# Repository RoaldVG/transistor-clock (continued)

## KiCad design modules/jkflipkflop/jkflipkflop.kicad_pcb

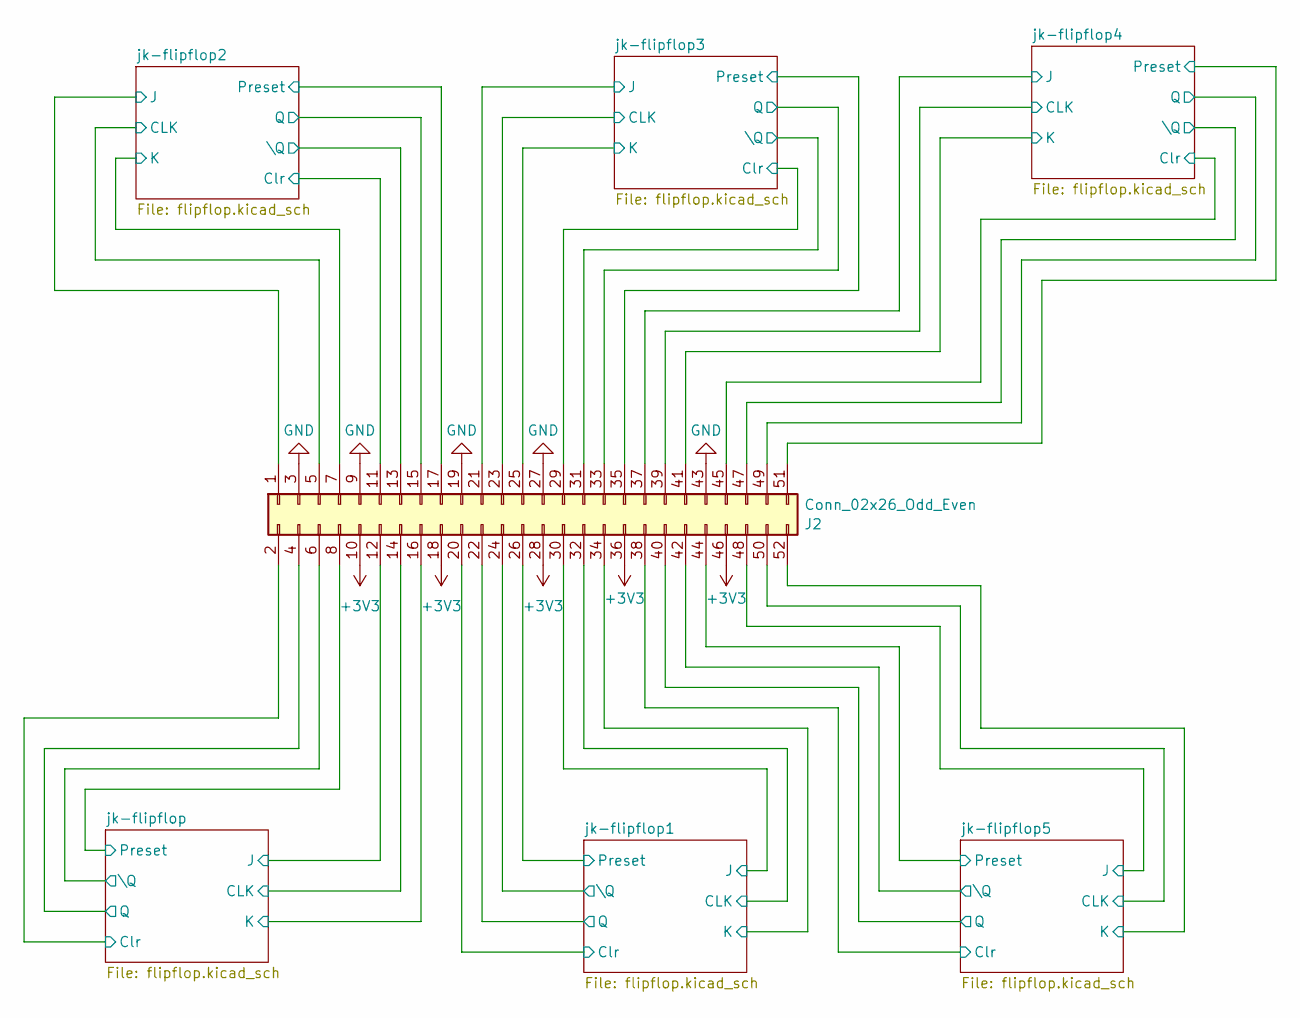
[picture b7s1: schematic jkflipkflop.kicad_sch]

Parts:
J2: Conn_02x26_Odd_Even; mpcie-full-card

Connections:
+3V3: J2.10, J2.18, J2.28, J2.36, J2.46; also elsewhere on the board
/jk-flipflop1/CLK: J2.32; also elsewhere on the board
/jk-flipflop1/Clr: J2.20; also elsewhere on the board
/jk-flipflop1/J: J2.30; also elsewhere on the board
/jk-flipflop1/K: J2.34; also elsewhere on the board
/jk-flipflop1/Preset: J2.26; also elsewhere on the board
/jk-flipflop1/Q: J2.22; also elsewhere on the board
/jk-flipflop1/\Q: J2.24; also elsewhere on the board
/jk-flipflop2/CLK: J2.5; also elsewhere on the board
/jk-flipflop2/Clr: J2.11; also elsewhere on the board
/jk-flipflop2/J: J2.1; also elsewhere on the board
/jk-flipflop2/K: J2.7; also elsewhere on the board
/jk-flipflop2/Preset: J2.17; also elsewhere on the board
/jk-flipflop2/Q: J2.15; also elsewhere on the board
/jk-flipflop2/\Q: J2.13; also elsewhere on the board
/jk-flipflop3/CLK: J2.23; also elsewhere on the board
/jk-flipflop3/Clr: J2.29; also elsewhere on the board
/jk-flipflop3/J: J2.21; also elsewhere on the board
/jk-flipflop3/K: J2.25; also elsewhere on the board
/jk-flipflop3/Preset: J2.35; also elsewhere on the board
/jk-flipflop3/Q: J2.33; also elsewhere on the board
/jk-flipflop3/\Q: J2.31; also elsewhere on the board
/jk-flipflop4/CLK: J2.39; also elsewhere on the board
/jk-flipflop4/Clr: J2.45; also elsewhere on the board
/jk-flipflop4/J: J2.37; also elsewhere on the board
/jk-flipflop4/K: J2.41; also elsewhere on the board
/jk-flipflop4/Preset: J2.51; also elsewhere on the board
/jk-flipflop4/Q: J2.49; also elsewhere on the board
/jk-flipflop4/\Q: J2.47; also elsewhere on the board
/jk-flipflop5/CLK: J2.50; also elsewhere on the board
/jk-flipflop5/Clr: J2.38; also elsewhere on the board
/jk-flipflop5/J: J2.48; also elsewhere on the board
/jk-flipflop5/K: J2.52; also elsewhere on the board
/jk-flipflop5/Preset: J2.44; also elsewhere on the board
/jk-flipflop5/Q: J2.40; also elsewhere on the board
/jk-flipflop5/\Q: J2.42; also elsewhere on the board
/jk-flipflop/CLK: J2.14; also elsewhere on the board
/jk-flipflop/Clr: J2.2; also elsewhere on the board
/jk-flipflop/J: J2.12; also elsewhere on the board
/jk-flipflop/K: J2.16; also elsewhere on the board
/jk-flipflop/Preset: J2.8; also elsewhere on the board
/jk-flipflop/Q: J2.4; also elsewhere on the board
/jk-flipflop/\Q: J2.6; also elsewhere on the board
GND: J2.3, J2.9, J2.19, J2.27, J2.43; also elsewhere on the board

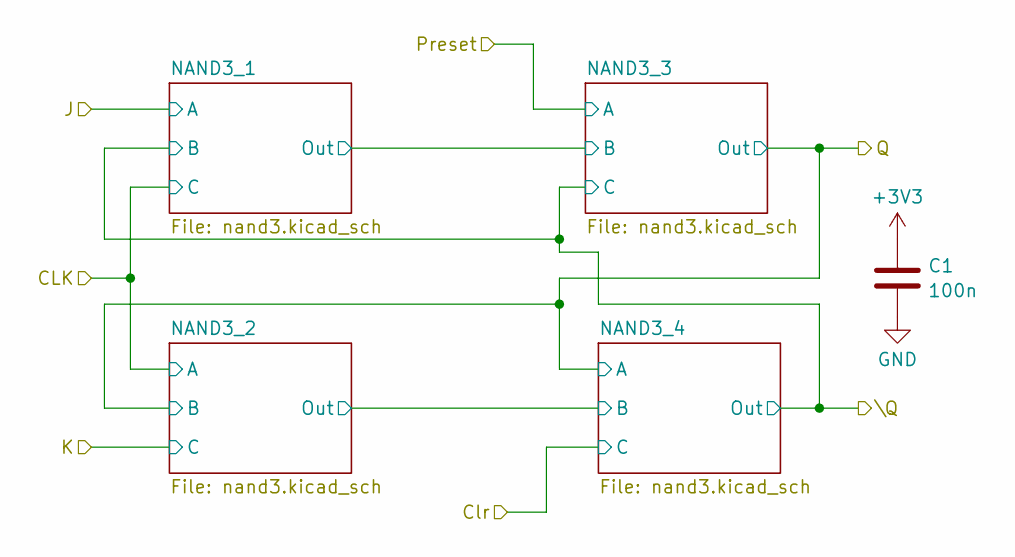
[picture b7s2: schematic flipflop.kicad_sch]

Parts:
C1: 100n; C_0603_1608Metric

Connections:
+3V3: C1.1; also elsewhere on the board
GND: C1.2; also elsewhere on the board

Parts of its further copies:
C2, C3, C4, C5, C6: 100n; C_0603_1608Metric

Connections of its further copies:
+3V3: C2.1, C3.1, C4.1, C5.1, C6.1; also elsewhere on the board
GND: C2.2, C3.2, C4.2, C5.2, C6.2; also elsewhere on the board

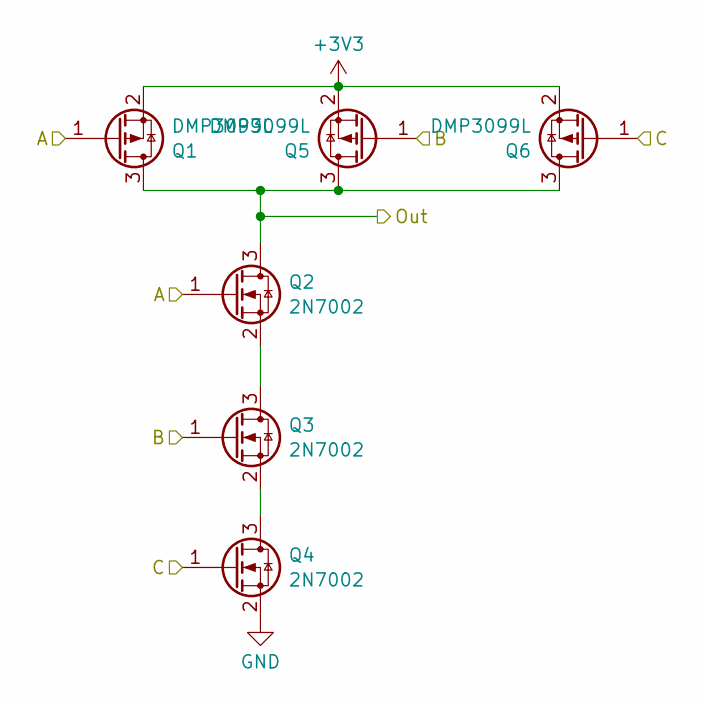
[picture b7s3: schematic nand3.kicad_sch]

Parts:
Q1, Q5, Q6: DMP3099L; SOT-23
Q2, Q3, Q4: 2N7002; SOT-23

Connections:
+3V3: Q1.2 (S), Q5.2 (S), Q6.2 (S); also elsewhere on the board
/jk-flipflop1/CLK: Q1.1 (G), Q2.1 (G); also elsewhere on the board
/jk-flipflop1/K: Q4.1 (G), Q6.1 (G); also elsewhere on the board
/jk-flipflop1/NAND3_2/Out: Q1.3 (D), Q2.3 (D), Q5.3 (D), Q6.3 (D); also elsewhere on the board
/jk-flipflop1/Q: Q3.1 (G), Q5.1 (G); also elsewhere on the board
GND: Q4.2 (S); also elsewhere on the board
unnamed: Q2.2 (S), Q3.3 (D)
unnamed: Q3.2 (S), Q4.3 (D)

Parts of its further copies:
Q7, Q11, Q12, Q13, Q17, Q18, Q19, Q23, Q24, Q25, Q29, Q30, Q31, Q35, Q36, Q37, Q41, Q42, Q43, Q47, Q48, Q49, Q50, Q57, Q58, Q59, Q60, Q61, Q62, Q69, Q70, Q71, Q72, Q73, Q74, Q81, Q82, Q83, Q84, Q85, Q86, Q93, Q94, Q95, Q96, Q97, Q101, Q102, Q103, Q107, Q108, Q109, Q113, Q114, Q115, Q119, Q120, Q121, Q125, Q126, Q127, Q131, Q132, Q133, Q137, Q138, Q139, Q143, Q144: DMP3099L; SOT-23
Q8, Q9, Q10, Q14, Q15, Q16, Q20, Q21, Q22, Q26, Q27, Q28, Q32, Q33, Q34, Q38, Q39, Q40, Q44, Q45, Q46, Q51, Q52, Q53, Q54, Q55, Q56, Q63, Q64, Q65, Q66, Q67, Q68, Q75, Q76, Q77, Q78, Q79, Q80, Q87, Q88, Q89, Q90, Q91, Q92, Q98, Q99, Q100, Q104, Q105, Q106, Q110, Q111, Q112, Q116, Q117, Q118, Q122, Q123, Q124, Q128, Q129, Q130, Q134, Q135, Q136, Q140, Q141, Q142: 2N7002; SOT-23

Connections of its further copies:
+3V3: Q7.2 (S), Q11.2 (S), Q12.2 (S), Q13.2 (S), Q17.2 (S), Q18.2 (S), Q19.2 (S), Q23.2 (S), Q24.2 (S), Q25.2 (S), Q29.2 (S), Q30.2 (S), Q31.2 (S), Q35.2 (S), Q36.2 (S), Q37.2 (S), Q41.2 (S), Q42.2 (S), Q43.2 (S), Q47.2 (S), Q48.2 (S), Q49.2 (S), Q50.2 (S), Q57.2 (S), Q58.2 (S), Q59.2 (S), Q60.2 (S), Q61.2 (S), Q62.2 (S), Q69.2 (S), Q70.2 (S), Q71.2 (S), Q72.2 (S), Q73.2 (S), Q74.2 (S), Q81.2 (S), Q82.2 (S), Q83.2 (S), Q84.2 (S), Q85.2 (S), Q86.2 (S), Q93.2 (S), Q94.2 (S), Q95.2 (S), Q96.2 (S), Q97.2 (S), Q101.2 (S), Q102.2 (S), Q103.2 (S), Q107.2 (S), Q108.2 (S), Q109.2 (S), Q113.2 (S), Q114.2 (S), Q115.2 (S), Q119.2 (S), Q120.2 (S), Q121.2 (S), Q125.2 (S), Q126.2 (S), Q127.2 (S), Q131.2 (S), Q132.2 (S), Q133.2 (S), Q137.2 (S), Q138.2 (S), Q139.2 (S), Q143.2 (S), Q144.2 (S); also elsewhere on the board
/jk-flipflop1/CLK: Q10.1 (G), Q12.1 (G); also elsewhere on the board
/jk-flipflop1/Clr: Q46.1 (G), Q48.1 (G); also elsewhere on the board
/jk-flipflop1/J: Q7.1 (G), Q8.1 (G); also elsewhere on the board
/jk-flipflop1/NAND3_1/Out: Q7.3 (D), Q8.3 (D), Q11.3 (D), Q12.3 (D), Q15.1 (G), Q17.1 (G)
/jk-flipflop1/NAND3_2/Out: Q45.1 (G), Q47.1 (G); also elsewhere on the board
/jk-flipflop1/Preset: Q13.1 (G), Q14.1 (G); also elsewhere on the board
/jk-flipflop1/Q: Q13.3 (D), Q14.3 (D), Q17.3 (D), Q18.3 (D), Q43.1 (G), Q44.1 (G); also elsewhere on the board
/jk-flipflop1/\Q: Q9.1 (G), Q11.1 (G), Q16.1 (G), Q18.1 (G), Q43.3 (D), Q44.3 (D), Q47.3 (D), Q48.3 (D); also elsewhere on the board
/jk-flipflop2/CLK: Q56.1 (G), Q59.1 (G), Q61.1 (G), Q63.1 (G); also elsewhere on the board
/jk-flipflop2/Clr: Q92.1 (G), Q95.1 (G); also elsewhere on the board
/jk-flipflop2/J: Q50.1 (G), Q52.1 (G); also elsewhere on the board
/jk-flipflop2/K: Q68.1 (G), Q71.1 (G); also elsewhere on the board
/jk-flipflop2/NAND3_1/Out: Q50.3 (D), Q52.3 (D), Q58.3 (D), Q59.3 (D), Q78.1 (G), Q82.1 (G)
/jk-flipflop2/NAND3_2/Out: Q61.3 (D), Q63.3 (D), Q70.3 (D), Q71.3 (D), Q90.1 (G), Q94.1 (G)
/jk-flipflop2/Preset: Q73.1 (G), Q75.1 (G); also elsewhere on the board
/jk-flipflop2/Q: Q66.1 (G), Q70.1 (G), Q73.3 (D), Q75.3 (D), Q82.3 (D), Q84.3 (D), Q86.1 (G), Q88.1 (G); also elsewhere on the board
/jk-flipflop2/\Q: Q53.1 (G), Q58.1 (G), Q79.1 (G), Q84.1 (G), Q86.3 (D), Q88.3 (D), Q94.3 (D), Q95.3 (D); also elsewhere on the board
/jk-flipflop3/CLK: Q49.1 (G), Q51.1 (G), Q67.1 (G), Q72.1 (G); also elsewhere on the board
/jk-flipflop3/Clr: Q91.1 (G), Q96.1 (G); also elsewhere on the board
/jk-flipflop3/J: Q62.1 (G), Q64.1 (G); also elsewhere on the board
/jk-flipflop3/K: Q55.1 (G), Q60.1 (G); also elsewhere on the board
/jk-flipflop3/NAND3_1/Out: Q62.3 (D), Q64.3 (D), Q69.3 (D), Q72.3 (D), Q77.1 (G), Q81.1 (G)
/jk-flipflop3/NAND3_2/Out: Q49.3 (D), Q51.3 (D), Q57.3 (D), Q60.3 (D), Q89.1 (G), Q93.1 (G)
/jk-flipflop3/Preset: Q74.1 (G), Q76.1 (G); also elsewhere on the board
/jk-flipflop3/Q: Q54.1 (G), Q57.1 (G), Q74.3 (D), Q76.3 (D), Q81.3 (D), Q83.3 (D), Q85.1 (G), Q87.1 (G); also elsewhere on the board
/jk-flipflop3/\Q: Q65.1 (G), Q69.1 (G), Q80.1 (G), Q83.1 (G), Q85.3 (D), Q87.3 (D), Q93.3 (D), Q96.3 (D); also elsewhere on the board
/jk-flipflop4/CLK: Q112.1 (G), Q114.1 (G), Q115.1 (G), Q116.1 (G); also elsewhere on the board
/jk-flipflop4/Clr: Q106.1 (G), Q108.1 (G); also elsewhere on the board
/jk-flipflop4/J: Q109.1 (G), Q110.1 (G); also elsewhere on the board
/jk-flipflop4/K: Q118.1 (G), Q120.1 (G); also elsewhere on the board
/jk-flipflop4/NAND3_1/Out: Q99.1 (G), Q101.1 (G), Q109.3 (D), Q110.3 (D), Q113.3 (D), Q114.3 (D)
/jk-flipflop4/NAND3_2/Out: Q105.1 (G), Q107.1 (G), Q115.3 (D), Q116.3 (D), Q119.3 (D), Q120.3 (D)
/jk-flipflop4/Preset: Q97.1 (G), Q98.1 (G); also elsewhere on the board
/jk-flipflop4/Q: Q97.3 (D), Q98.3 (D), Q101.3 (D), Q102.3 (D), Q103.1 (G), Q104.1 (G), Q117.1 (G), Q119.1 (G); also elsewhere on the board
/jk-flipflop4/\Q: Q100.1 (G), Q102.1 (G), Q103.3 (D), Q104.3 (D), Q107.3 (D), Q108.3 (D), Q111.1 (G), Q113.1 (G); also elsewhere on the board
/jk-flipflop5/CLK: Q136.1 (G), Q138.1 (G), Q139.1 (G), Q140.1 (G); also elsewhere on the board
/jk-flipflop5/Clr: Q130.1 (G), Q132.1 (G); also elsewhere on the board
/jk-flipflop5/J: Q133.1 (G), Q134.1 (G); also elsewhere on the board
/jk-flipflop5/K: Q142.1 (G), Q144.1 (G); also elsewhere on the board
/jk-flipflop5/NAND3_1/Out: Q123.1 (G), Q125.1 (G), Q133.3 (D), Q134.3 (D), Q137.3 (D), Q138.3 (D)
/jk-flipflop5/NAND3_2/Out: Q129.1 (G), Q131.1 (G), Q139.3 (D), Q140.3 (D), Q143.3 (D), Q144.3 (D)
/jk-flipflop5/Preset: Q121.1 (G), Q122.1 (G); also elsewhere on the board
/jk-flipflop5/Q: Q121.3 (D), Q122.3 (D), Q125.3 (D), Q126.3 (D), Q127.1 (G), Q128.1 (G), Q141.1 (G), Q143.1 (G); also elsewhere on the board
/jk-flipflop5/\Q: Q124.1 (G), Q126.1 (G), Q127.3 (D), Q128.3 (D), Q131.3 (D), Q132.3 (D), Q135.1 (G), Q137.1 (G); also elsewhere on the board
/jk-flipflop/CLK: Q22.1 (G), Q24.1 (G), Q25.1 (G), Q26.1 (G); also elsewhere on the board
/jk-flipflop/Clr: Q40.1 (G), Q42.1 (G); also elsewhere on the board
/jk-flipflop/J: Q19.1 (G), Q20.1 (G); also elsewhere on the board
/jk-flipflop/K: Q28.1 (G), Q30.1 (G); also elsewhere on the board
/jk-flipflop/NAND3_1/Out: Q19.3 (D), Q20.3 (D), Q23.3 (D), Q24.3 (D), Q33.1 (G), Q35.1 (G)
/jk-flipflop/NAND3_2/Out: Q25.3 (D), Q26.3 (D), Q29.3 (D), Q30.3 (D), Q39.1 (G), Q41.1 (G)
/jk-flipflop/Preset: Q31.1 (G), Q32.1 (G); also elsewhere on the board
/jk-flipflop/Q: Q27.1 (G), Q29.1 (G), Q31.3 (D), Q32.3 (D), Q35.3 (D), Q36.3 (D), Q37.1 (G), Q38.1 (G); also elsewhere on the board
/jk-flipflop/\Q: Q21.1 (G), Q23.1 (G), Q34.1 (G), Q36.1 (G), Q37.3 (D), Q38.3 (D), Q41.3 (D), Q42.3 (D); also elsewhere on the board
GND: Q10.2 (S), Q16.2 (S), Q22.2 (S), Q28.2 (S), Q34.2 (S), Q40.2 (S), Q46.2 (S), Q55.2 (S), Q56.2 (S), Q67.2 (S), Q68.2 (S), Q79.2 (S), Q80.2 (S), Q91.2 (S), Q92.2 (S), Q100.2 (S), Q106.2 (S), Q112.2 (S), Q118.2 (S), Q124.2 (S), Q130.2 (S), Q136.2 (S), Q142.2 (S); also elsewhere on the board
unnamed: Q8.2 (S), Q9.3 (D)
unnamed: Q9.2 (S), Q10.3 (D)
unnamed: Q14.2 (S), Q15.3 (D)
unnamed: Q15.2 (S), Q16.3 (D)
unnamed: Q20.2 (S), Q21.3 (D)
unnamed: Q21.2 (S), Q22.3 (D)
unnamed: Q26.2 (S), Q27.3 (D)
unnamed: Q27.2 (S), Q28.3 (D)
unnamed: Q32.2 (S), Q33.3 (D)
unnamed: Q33.2 (S), Q34.3 (D)
unnamed: Q38.2 (S), Q39.3 (D)
unnamed: Q39.2 (S), Q40.3 (D)
unnamed: Q44.2 (S), Q45.3 (D)
unnamed: Q45.2 (S), Q46.3 (D)
unnamed: Q51.2 (S), Q54.3 (D)
unnamed: Q52.2 (S), Q53.3 (D)
unnamed: Q53.2 (S), Q56.3 (D)
unnamed: Q54.2 (S), Q55.3 (D)
unnamed: Q63.2 (S), Q66.3 (D)
unnamed: Q64.2 (S), Q65.3 (D)
unnamed: Q65.2 (S), Q67.3 (D)
unnamed: Q66.2 (S), Q68.3 (D)
unnamed: Q75.2 (S), Q78.3 (D)
unnamed: Q76.2 (S), Q77.3 (D)
unnamed: Q77.2 (S), Q80.3 (D)
unnamed: Q78.2 (S), Q79.3 (D)
unnamed: Q87.2 (S), Q89.3 (D)
unnamed: Q88.2 (S), Q90.3 (D)
unnamed: Q89.2 (S), Q91.3 (D)
unnamed: Q90.2 (S), Q92.3 (D)
unnamed: Q98.2 (S), Q99.3 (D)
unnamed: Q99.2 (S), Q100.3 (D)
unnamed: Q104.2 (S), Q105.3 (D)
unnamed: Q105.2 (S), Q106.3 (D)
unnamed: Q110.2 (S), Q111.3 (D)
unnamed: Q111.2 (S), Q112.3 (D)
unnamed: Q116.2 (S), Q117.3 (D)
unnamed: Q117.2 (S), Q118.3 (D)
unnamed: Q122.2 (S), Q123.3 (D)
unnamed: Q123.2 (S), Q124.3 (D)
unnamed: Q128.2 (S), Q129.3 (D)
unnamed: Q129.2 (S), Q130.3 (D)
unnamed: Q134.2 (S), Q135.3 (D)
unnamed: Q135.2 (S), Q136.3 (D)
unnamed: Q140.2 (S), Q141.3 (D)
unnamed: Q141.2 (S), Q142.3 (D)

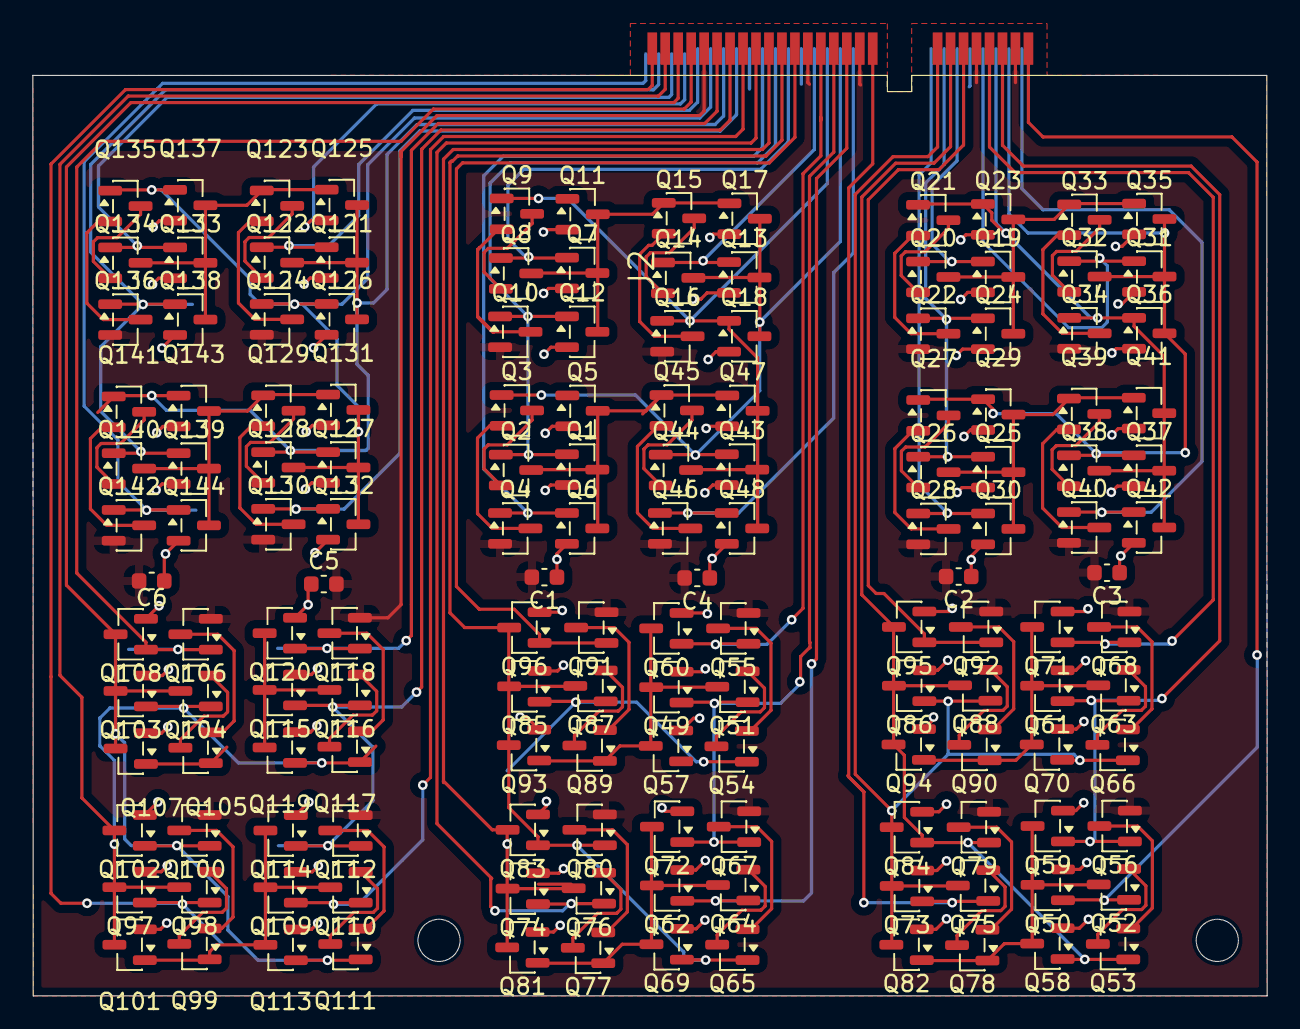
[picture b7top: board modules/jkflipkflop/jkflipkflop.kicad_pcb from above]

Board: 2 copper layers, 76.1 x 56.8 mm, 151 parts (0 on the bottom side), 104 nets.

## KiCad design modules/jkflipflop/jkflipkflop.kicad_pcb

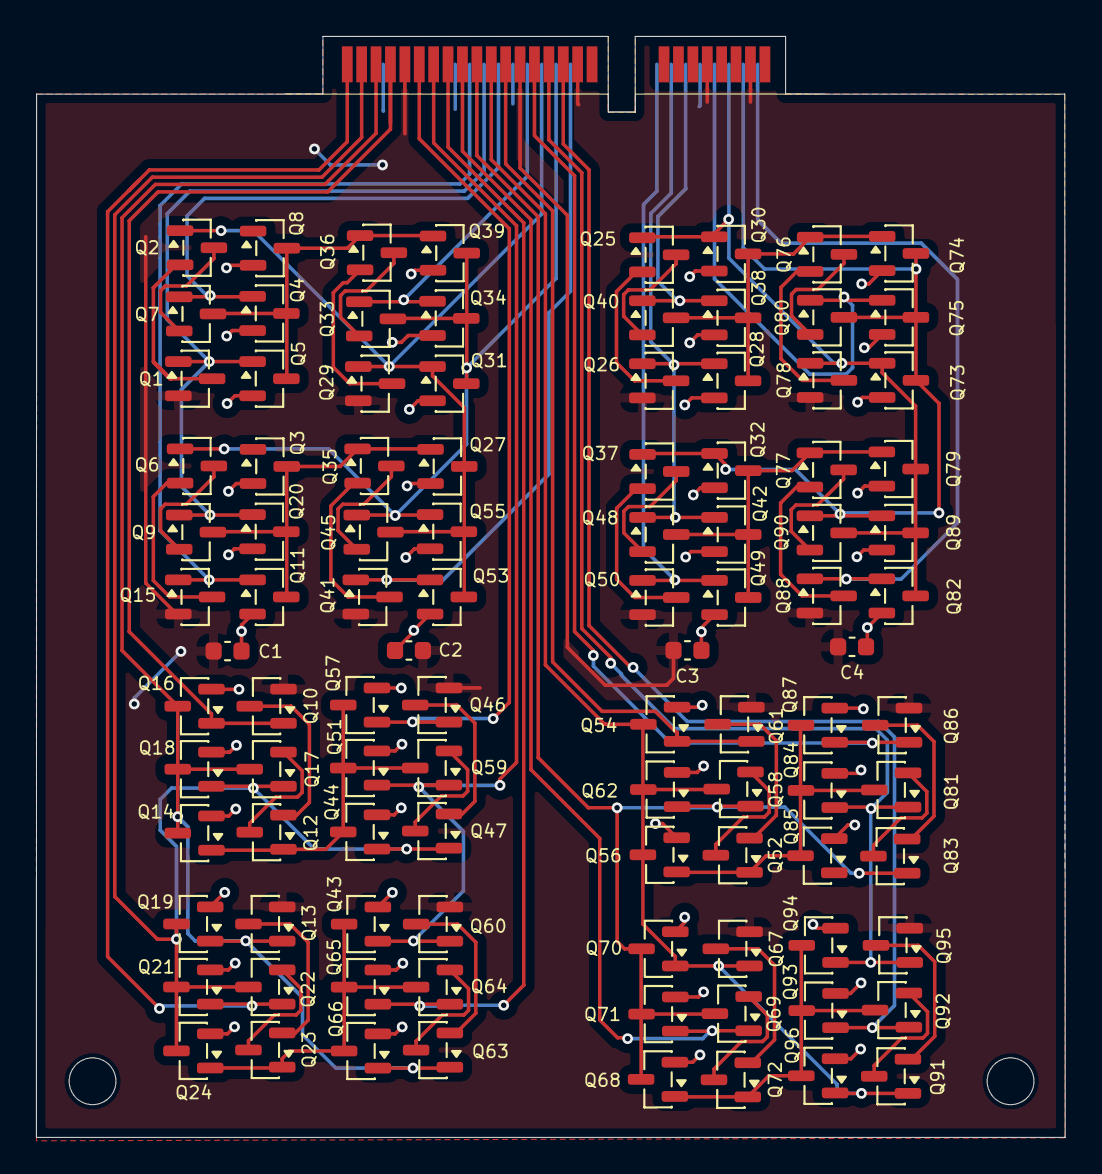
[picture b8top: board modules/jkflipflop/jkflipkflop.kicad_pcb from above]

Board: 2 copper layers, 57.2 x 61.2 mm, 101 parts (0 on the bottom side), 70 nets.

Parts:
C1, C2, C3, C4: 100n; C_0603_1608Metric
J1: Conn_02x26_Odd_Even; mpcie-full-card
Q1, Q2, Q6, Q7, Q9, Q10, Q12, Q13, Q15, Q17, Q22, Q23, Q25, Q26, Q29, Q33, Q35, Q36, Q37, Q40, Q41, Q45, Q46, Q47, Q48, Q50, Q52, Q58, Q59, Q60, Q61, Q63, Q64, Q67, Q69, Q72, Q76, Q77, Q78, Q80, Q81, Q83, Q86, Q88, Q90, Q91, Q92, Q95: 2N7002; SOT-23
Q3, Q4, Q5, Q8, Q11, Q14, Q16, Q18, Q19, Q20, Q21, Q24, Q27, Q28, Q30, Q31, Q32, Q34, Q38, Q39, Q42, Q43, Q44, Q49, Q51, Q53, Q54, Q55, Q56, Q57, Q62, Q65, Q66, Q68, Q70, Q71, Q73, Q74, Q75, Q79, Q82, Q84, Q85, Q87, Q89, Q93, Q94, Q96: AO3401A; SOT-23

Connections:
+3V3: C1.1, C2.1, C3.1, C4.1, J1.10, J1.18, J1.28, J1.36, J1.46, Q3.2 (S), Q4.2 (S), Q5.2 (S), Q8.2 (S), Q11.2 (S), Q14.2 (S), Q16.2 (S), Q18.2 (S), Q19.2 (S), Q20.2 (S), Q21.2 (S), Q24.2 (S), Q27.2 (S), Q28.2 (S), Q30.2 (S), Q31.2 (S), Q32.2 (S), Q34.2 (S), Q38.2 (S), Q39.2 (S), Q42.2 (S), Q43.2 (S), Q44.2 (S), Q49.2 (S), Q51.2 (S), Q53.2 (S), Q54.2 (S), Q55.2 (S), Q56.2 (S), Q57.2 (S), Q62.2 (S), Q65.2 (S), Q66.2 (S), Q68.2 (S), Q70.2 (S), Q71.2 (S), Q73.2 (S), Q74.2 (S), Q75.2 (S), Q79.2 (S), Q82.2 (S), Q84.2 (S), Q85.2 (S), Q87.2 (S), Q89.2 (S), Q93.2 (S), Q94.2 (S), Q96.2 (S)
/jk-flipflop1/CLK: J1.32, Q1.1 (G), Q5.1 (G), Q9.1 (G), Q20.1 (G)
/jk-flipflop1/Clr: J1.20, Q41.1 (G), Q53.1 (G)
/jk-flipflop1/J: J1.30, Q4.1 (G), Q7.1 (G)
/jk-flipflop1/K: J1.34, Q11.1 (G), Q15.1 (G)
/jk-flipflop1/NAND3_1/Out: Q4.3 (D), Q5.3 (D), Q7.3 (D), Q8.3 (D), Q36.1 (G), Q39.1 (G)
/jk-flipflop1/NAND3_2/Out: Q3.3 (D), Q9.3 (D), Q11.3 (D), Q20.3 (D), Q27.1 (G), Q35.1 (G)
/jk-flipflop1/Preset: J1.26, Q33.1 (G), Q34.1 (G)
/jk-flipflop1/Q: J1.22, Q3.1 (G), Q6.1 (G), Q31.3 (D), Q33.3 (D), Q34.3 (D), Q39.3 (D), Q45.1 (G), Q55.1 (G)
/jk-flipflop1/\Q: J1.24, Q2.1 (G), Q8.1 (G), Q27.3 (D), Q29.1 (G), Q31.1 (G), Q45.3 (D), Q53.3 (D), Q55.3 (D)
/jk-flipflop3/CLK: J1.23, Q81.1 (G), Q84.1 (G), Q94.1 (G), Q95.1 (G)
/jk-flipflop3/Clr: J1.29, Q54.1 (G), Q61.1 (G)
/jk-flipflop3/J: J1.21, Q92.1 (G), Q93.1 (G)
/jk-flipflop3/K: J1.25, Q86.1 (G), Q87.1 (G)
/jk-flipflop3/NAND3_1/Out: Q68.1 (G), Q72.1 (G), Q92.3 (D), Q93.3 (D), Q94.3 (D), Q96.3 (D)
/jk-flipflop3/NAND3_2/Out: Q52.1 (G), Q56.1 (G), Q81.3 (D), Q84.3 (D), Q85.3 (D), Q87.3 (D)
/jk-flipflop3/Preset: J1.35, Q69.1 (G), Q71.1 (G)
/jk-flipflop3/Q: J1.33, Q58.1 (G), Q62.1 (G), Q68.3 (D), Q69.3 (D), Q70.3 (D), Q71.3 (D), Q83.1 (G), Q85.1 (G)
/jk-flipflop3/\Q: J1.31, Q54.3 (D), Q56.3 (D), Q58.3 (D), Q62.3 (D), Q67.1 (G), Q70.1 (G), Q91.1 (G), Q96.1 (G)
/jk-flipflop4/CLK: J1.39, Q43.1 (G), Q51.1 (G), Q59.1 (G), Q60.1 (G)
/jk-flipflop4/Clr: J1.45, Q10.1 (G), Q16.1 (G)
/jk-flipflop4/J: J1.37, Q64.1 (G), Q65.1 (G)
/jk-flipflop4/K: J1.41, Q46.1 (G), Q57.1 (G)
/jk-flipflop4/NAND3_1/Out: Q23.1 (G), Q24.1 (G), Q43.3 (D), Q64.3 (D), Q65.3 (D), Q66.3 (D)
/jk-flipflop4/NAND3_2/Out: Q12.1 (G), Q14.1 (G), Q44.3 (D), Q51.3 (D), Q57.3 (D), Q59.3 (D)
/jk-flipflop4/Preset: J1.51, Q21.1 (G), Q22.1 (G)
/jk-flipflop4/Q: J1.49, Q17.1 (G), Q18.1 (G), Q19.3 (D), Q21.3 (D), Q22.3 (D), Q24.3 (D), Q44.1 (G), Q47.1 (G)
/jk-flipflop4/\Q: J1.47, Q13.1 (G), Q14.3 (D), Q16.3 (D), Q17.3 (D), Q18.3 (D), Q19.1 (G), Q63.1 (G), Q66.1 (G)
/jk-flipflop/CLK: J1.14, Q26.1 (G), Q28.1 (G), Q42.1 (G), Q48.1 (G)
/jk-flipflop/Clr: J1.2, Q82.1 (G), Q88.1 (G)
/jk-flipflop/J: J1.12, Q38.1 (G), Q40.1 (G)
/jk-flipflop/K: J1.16, Q49.1 (G), Q50.1 (G)
/jk-flipflop/NAND3_1/Out: Q28.3 (D), Q30.3 (D), Q38.3 (D), Q40.3 (D), Q74.1 (G), Q76.1 (G)
/jk-flipflop/NAND3_2/Out: Q32.3 (D), Q42.3 (D), Q48.3 (D), Q49.3 (D), Q77.1 (G), Q79.1 (G)
/jk-flipflop/Preset: J1.8, Q75.1 (G), Q80.1 (G)
/jk-flipflop/Q: J1.4, Q32.1 (G), Q37.1 (G), Q73.3 (D), Q74.3 (D), Q75.3 (D), Q80.3 (D), Q89.1 (G), Q90.1 (G)
/jk-flipflop/\Q: J1.6, Q25.1 (G), Q30.1 (G), Q73.1 (G), Q78.1 (G), Q79.3 (D), Q82.3 (D), Q89.3 (D), Q90.3 (D)
GND: C1.2, C2.2, C3.2, C4.2, J1.3, J1.9, J1.19, J1.27, J1.43, Q1.2 (S), Q10.2 (S), Q13.2 (S), Q15.2 (S), Q26.2 (S), Q29.2 (S), Q41.2 (S), Q46.2 (S), Q50.2 (S), Q60.2 (S), Q61.2 (S), Q67.2 (S), Q78.2 (S), Q86.2 (S), Q88.2 (S), Q95.2 (S)
unnamed: Q6.3 (D), Q9.2 (S)
unnamed: Q6.2 (S), Q15.3 (D)
unnamed: Q2.3 (D), Q7.2 (S)
unnamed: Q1.3 (D), Q2.2 (S)
unnamed: Q33.2 (S), Q36.3 (D)
unnamed: Q29.3 (D), Q36.2 (S)
unnamed: Q25.3 (D), Q40.2 (S)
unnamed: Q25.2 (S), Q26.3 (D)
unnamed: Q37.3 (D), Q48.2 (S)
unnamed: Q37.2 (S), Q50.3 (D)
unnamed: Q76.3 (D), Q80.2 (S)
unnamed: Q76.2 (S), Q78.3 (D)
unnamed: Q77.3 (D), Q90.2 (S)
unnamed: Q77.2 (S), Q88.3 (D)
unnamed: Q35.3 (D), Q45.2 (S)
unnamed: Q35.2 (S), Q41.3 (D)
unnamed: Q81.2 (S), Q83.3 (D)
unnamed: Q83.2 (S), Q86.3 (D)
unnamed: Q91.3 (D), Q92.2 (S)
unnamed: Q91.2 (S), Q95.3 (D)
unnamed: Q69.2 (S), Q72.3 (D)
unnamed: Q67.3 (D), Q72.2 (S)
unnamed: Q52.3 (D), Q58.2 (S)
unnamed: Q52.2 (S), Q61.3 (D)
unnamed: Q22.2 (S), Q23.3 (D)
unnamed: Q13.3 (D), Q23.2 (S)
unnamed: Q12.3 (D), Q17.2 (S)
unnamed: Q10.3 (D), Q12.2 (S)
unnamed: Q63.3 (D), Q64.2 (S)
unnamed: Q60.3 (D), Q63.2 (S)
unnamed: Q47.3 (D), Q59.2 (S)
unnamed: Q46.3 (D), Q47.2 (S)

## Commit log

2026-02-28 init commit
2026-03-04 update ignored files
2026-03-04 moved to 3v3
2026-03-04 added decoupling caps
2026-03-04 moved simulations to seperate dir
2026-03-04 changed rectifier diodes
2026-03-05 corrected output/input type of pins
2026-03-05 started routing
2026-03-19 schematic cleanup, routed 1 bdc
2026-03-19 started modular approach
2026-03-20 changed from pcie x1 to mini pcie. added 2 flipflops
2026-03-20 started on binary to decimal converter
2026-03-21 routed on bdc
2026-03-25 went from routed bin-to-dec to gate only
2026-03-27 move to correct dir. improved symmetry of pcb
2026-03-27 DRC. added fab outputs
2026-03-30 using plugin to generate jlc production files
2026-03-30 move components to top layer :(
2026-03-30 switched to jlc basic components
2026-03-30 moved designators
2026-03-31 made library for modules
2026-03-31 replace bcd logic with bin-to-dec module
2026-03-31 flipflop fab output
2026-03-31 fixed typo
2026-03-31 minor edits
2026-03-31 actually corrected typo
2026-04-01 switched to using flipflop module
2026-04-01 schematic cleanup
2026-04-01 module for SSRs
2026-04-01 dunno
2026-04-01 production output for SSR module
2026-04-01 switched to using SSR module
2026-04-01 added LCSC part numbers
2026-04-07 rust code for calculating clock RC values
2026-04-07 added rust target dir, oops
2026-04-07 switched clock to bjt astable multivibrator
2026-04-08 changed some components to lcsc parts
2026-04-08 added footprints for modules
2026-04-08 added module for PSU
2026-04-11 some routing on main board
2026-04-13 routy mcRouteface
2026-04-14 routing
2026-04-14 investigating flipflop in ltspice
2026-04-14 flipflop wip
2026-04-15 flipflop routing wip
2026-04-15 routed flipflops
2026-04-15 updated production files
2026-04-15 remove unnessecary backups
2026-04-15 PSU production files
2026-04-15 old typo file
2026-04-15 forgot to caps on flipflop module
2026-04-15 cleanup and DRC
2026-04-15 PSU: added power led
2026-04-24 flipflop sims
2026-04-24 change clock to 2hz? does input flipflop half it?
